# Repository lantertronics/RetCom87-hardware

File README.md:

# RetCom87-hardware
These are expansion boards for the W65C265SXB development board by Western Design Center developed for the "RetCom87" homebrew computer project by my Retrofuturistic Hardware Vertically Integrated Project team at Georgia Tech. For details, see this YouTube playlist:

https://www.youtube.com/playlist?list=PLOunECWxELQQ03GeMmJSVX49A8VtCcbT9

Atari/Sega controller board: This works! See the Wiki for how to read the controller buttons and the example test code.

Sound board: The YM2149 soundchip board design has been tested on the breadboard, but the actual PCB hasn't been tested yet (I need to order it from JLCPCB). See the example test code.

Video board: The reset pin on TMS9118 is erroneously left disconnected on the PCB; I had to add a bodge wire to hook it to the W65C265SXB reset pin. The TMS9118 board currently sends out bright speckled video. I'm not sure what the issue is: https://youtu.be/yKsjV6f-HKg -- if anyone has any advice, please let me know: lanterma@ece.gatech.edu

These designs are dedicated to the public domain.

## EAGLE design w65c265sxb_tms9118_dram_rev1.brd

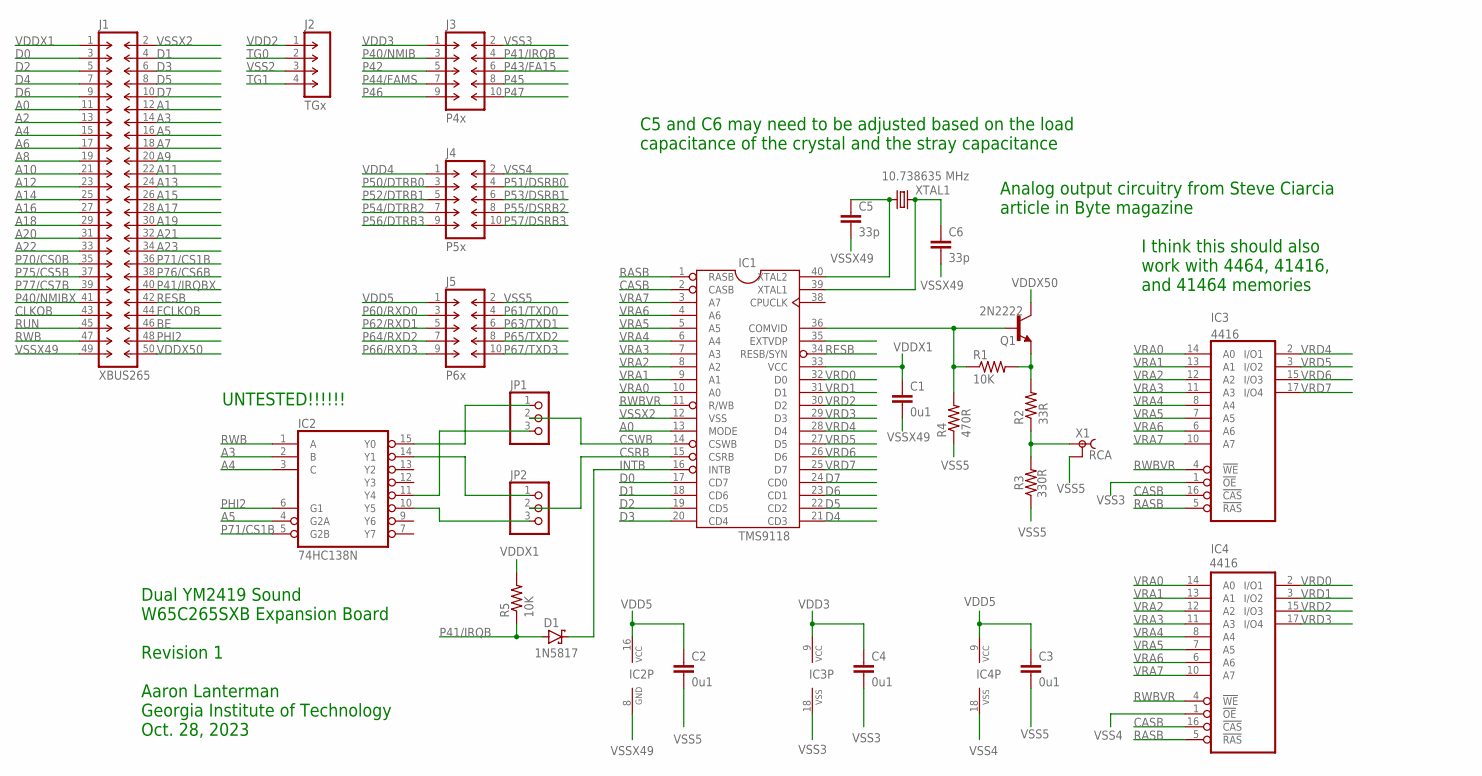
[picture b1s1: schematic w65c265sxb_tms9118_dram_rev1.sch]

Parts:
C1, C2, C3, C4: 0u1; C050-025X075-AARON
C5, C6: 33p; C050-025X075-AARON
D1: 1N5817-B; DO41-7.6
IC1: TMS9118; DIL40
IC2: 74HC138N; DIL16
IC3, IC4: 41464; DIL18
J1: XBUS265; DIL-100-2X25
J2: TGx; SIP-100-04-40
J3: P4x; DIL-100-2X05
J4: P5x; DIL-100-2X05
J5: P6x; DIL-100-2X05
JP1, JP2: PINHD-1X3; 1X03
Q1: 2N2222; TO92-EBC-OVAL
R1, R5: 10K; 0207/10
R2: 33R; 0207/10
R3: 330R; 0207/10
R4: 470R; 0207/10
X1: RCA; TOBU3
XTAL1: 10.738635 MHz; HC49/S

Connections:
A0: IC1.13 (MODE), J1.11
A1: J1.12
A2: J1.13
A3: IC2.2 (B), J1.14
A4: IC2.3 (C), J1.15
A5: IC2.4 (G2A), J1.16
A6: J1.17
A7: J1.18
A8: J1.19
A9: J1.20
A10: J1.21
A11: J1.22
A12: J1.23
A13: J1.24
A14: J1.25
A15: J1.26
A16: J1.27
A17: J1.28
A18: J1.29
A19: J1.30
A20: J1.31
A21: J1.32
A22: J1.33
A23: J1.34
BE: J1.46
CASB: IC1.2 (CASB), IC3.16 (!CAS), IC4.16 (!CAS)
CLKOB: J1.43
CSRB: IC1.15 (CSRB), JP2.2
CSWB: IC1.14 (CSWB), JP1.2
D0: IC1.17 (CD7), J1.3
D1: IC1.18 (CD6), J1.4
D2: IC1.19 (CD5), J1.5
D3: IC1.20 (CD4), J1.6
D4: IC1.21 (CD3), J1.7
D5: IC1.22 (CD2), J1.8
D6: IC1.23 (CD1), J1.9
D7: IC1.24 (CD0), J1.10
FCLKOB: J1.44
INTB: D1.C, IC1.16 (INTB)
unnamed: IC2.15 (Y0), JP1.1
unnamed: IC2.14 (Y1), JP2.1
unnamed: Q1.E, R1.2, R2.2
unnamed: R2.1, R3.2, X1.1
unnamed: IC2.11 (Y4), JP1.3
unnamed: IC2.10 (Y5), JP2.3
unnamed: IC1.36 (COMVID), Q1.B, R1.1, R4.2
P40/NMIB: J3.3
P40/NMIBX: J1.41
P41/IRQB: D1.A, J3.4, R5.1
P41/IRQBX: J1.40
P42: J3.5
P43/FA15: J3.6
P44/FAMS: J3.7
P45: J3.8
P46: J3.9
P47: J3.10
P50/DTRB0: J4.3
P51/DSRB0: J4.4
P52/DTRB1: J4.5
P53/DSRB1: J4.6
P54/DTRB2: J4.7
P55/DSRB2: J4.8
P56/DTRB3: J4.9
P57/DSRB3: J4.10
P60/RXD0: J5.3
P61/TXD0: J5.4
P62/RXD1: J5.5
P63/TXD1: J5.6
P64/RXD2: J5.7
P65/TXD2: J5.8
P66/RXD3: J5.9
P67/TXD3: J5.10
P70/CS0B: J1.35
P71/CS1B: IC2.5 (G2B), J1.36
P75/CS5B: J1.37
P76/CS6B: J1.38
P77/CS7B: J1.39
PHI2: IC2.6 (G1), J1.48
RASB: IC1.1 (RASB), IC3.5 (!RAS), IC4.5 (!RAS)
RESB: IC1.34 (RESB/SYN), J1.42
RUN: J1.45
RWB: IC2.1 (A), J1.47
RWBVR: IC1.11 (R/WB), IC3.4 (!WE), IC4.4 (!WE)
TG0: J2.2
TG1: J2.4
VDD2: J2.1
VDD3: C4.1, IC3.9 (VCC), J3.1
VDD4: J4.1
VDD5: C2.1, C3.1, IC2.16 (VCC), IC4.9 (VCC), J5.1
VDDX1: C1.1, IC1.33 (VCC), J1.1, R5.2
VDDX50: J1.50, Q1.C
VRA0: IC1.10 (A0), IC3.14 (A0), IC4.14 (A0)
VRA1: IC1.9 (A1), IC3.13 (A1), IC4.13 (A1)
VRA2: IC1.8 (A2), IC3.12 (A2), IC4.12 (A2)
VRA3: IC1.7 (A3), IC3.11 (A3), IC4.11 (A3)
VRA4: IC1.6 (A4), IC3.8 (A4), IC4.8 (A4)
VRA5: IC1.5 (A5), IC3.7 (A5), IC4.7 (A5)
VRA6: IC1.4 (A6), IC3.6 (A6), IC4.6 (A6)
VRA7: IC1.3 (A7), IC3.10 (A7), IC4.10 (A7)
VRD0: IC1.32 (D0), IC4.2 (I/O1)
VRD1: IC1.31 (D1), IC4.3 (I/O2)
VRD2: IC1.30 (D2), IC4.15 (I/O3)
VRD3: IC1.29 (D3), IC4.17 (I/O4)
VRD4: IC1.28 (D4), IC3.2 (I/O1)
VRD5: IC1.27 (D5), IC3.3 (I/O2)
VRD6: IC1.26 (D6), IC3.15 (I/O3)
VRD7: IC1.25 (D7), IC3.17 (I/O4)
VSS2: J2.3
VSS3: C4.2, IC3.1 (!OE), IC3.18 (VSS), J3.2
VSS4: IC4.1 (!OE), IC4.18 (VSS), J4.2
VSS5: C2.2, C3.2, J5.2, R3.1, R4.1, X1.2, X1.2@1 (2), X1.2@2 (2)
VSSX2: IC1.12 (VSS), J1.2
VSSX49: C1.2, C5.2, C6.2, IC2.8 (GND), J1.49
XTAL1: C6.1, IC1.39 (XTAL1), XTAL1.2
XTAL2: C5.1, IC1.40 (XTAL2), XTAL1.1

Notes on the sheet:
Dual YM2419 Sound W65C265SXB Expansion Board Revision 1 Aaron Lanterman Georgia Institute of Technology Oct. 28, 2023
UNTESTED!!!!!!
4416
I think this should also work with 4464, 41416, and 41464 memories
C5 and C6 may need to be adjusted based on the load capacitance of the crystal and the stray capacitance
Analog output circuitry from Steve Ciarcia article in Byte magazine
1N5817

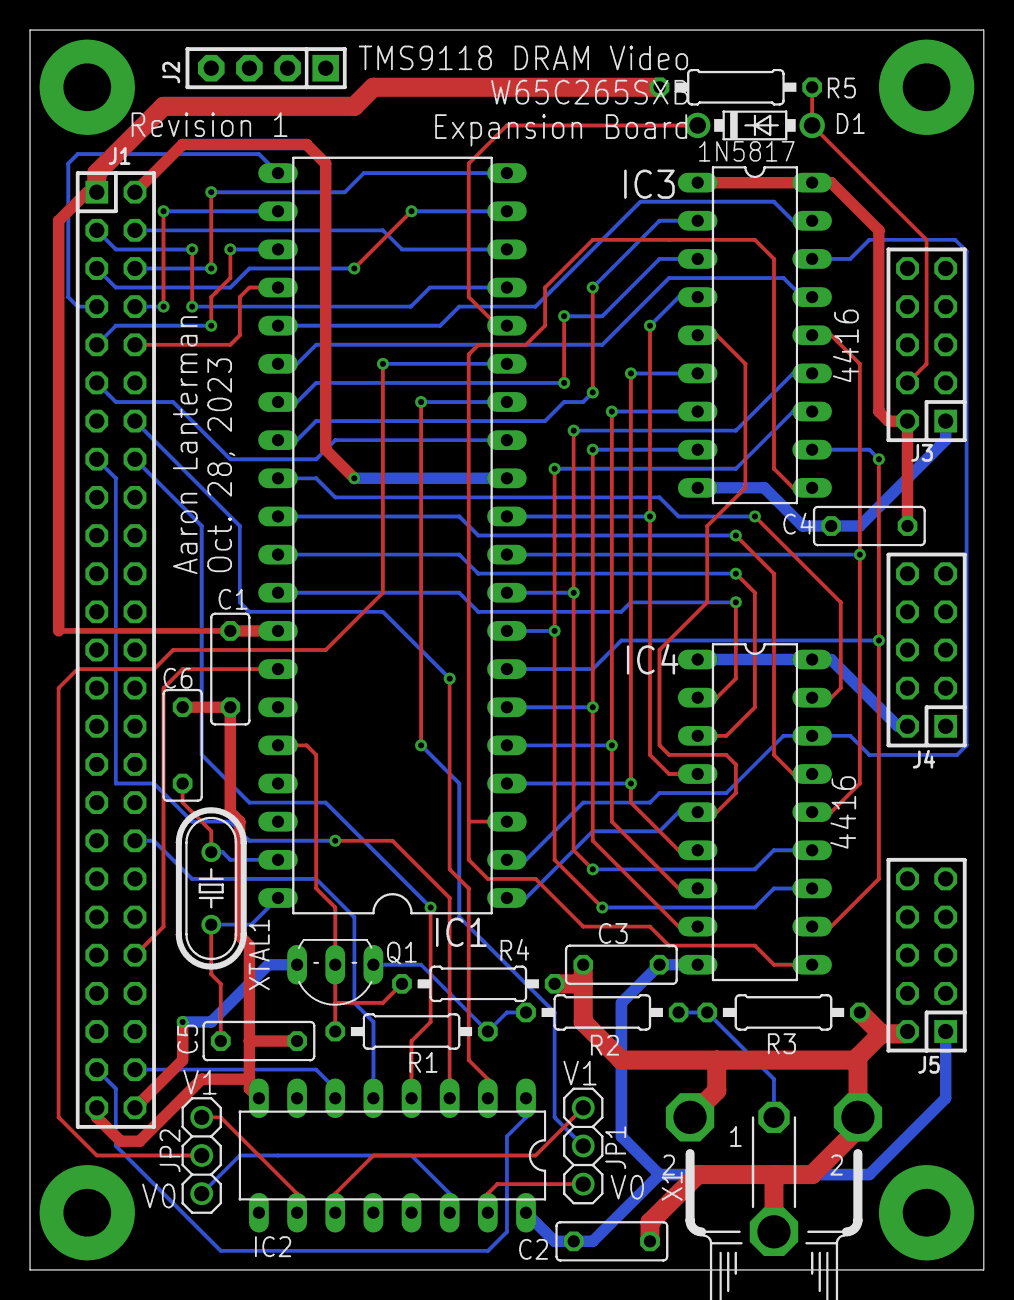
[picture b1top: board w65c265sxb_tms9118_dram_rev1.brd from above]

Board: 2 copper layers, 63.5 x 82.5 mm, 26 parts (0 on the bottom side), 57 nets.

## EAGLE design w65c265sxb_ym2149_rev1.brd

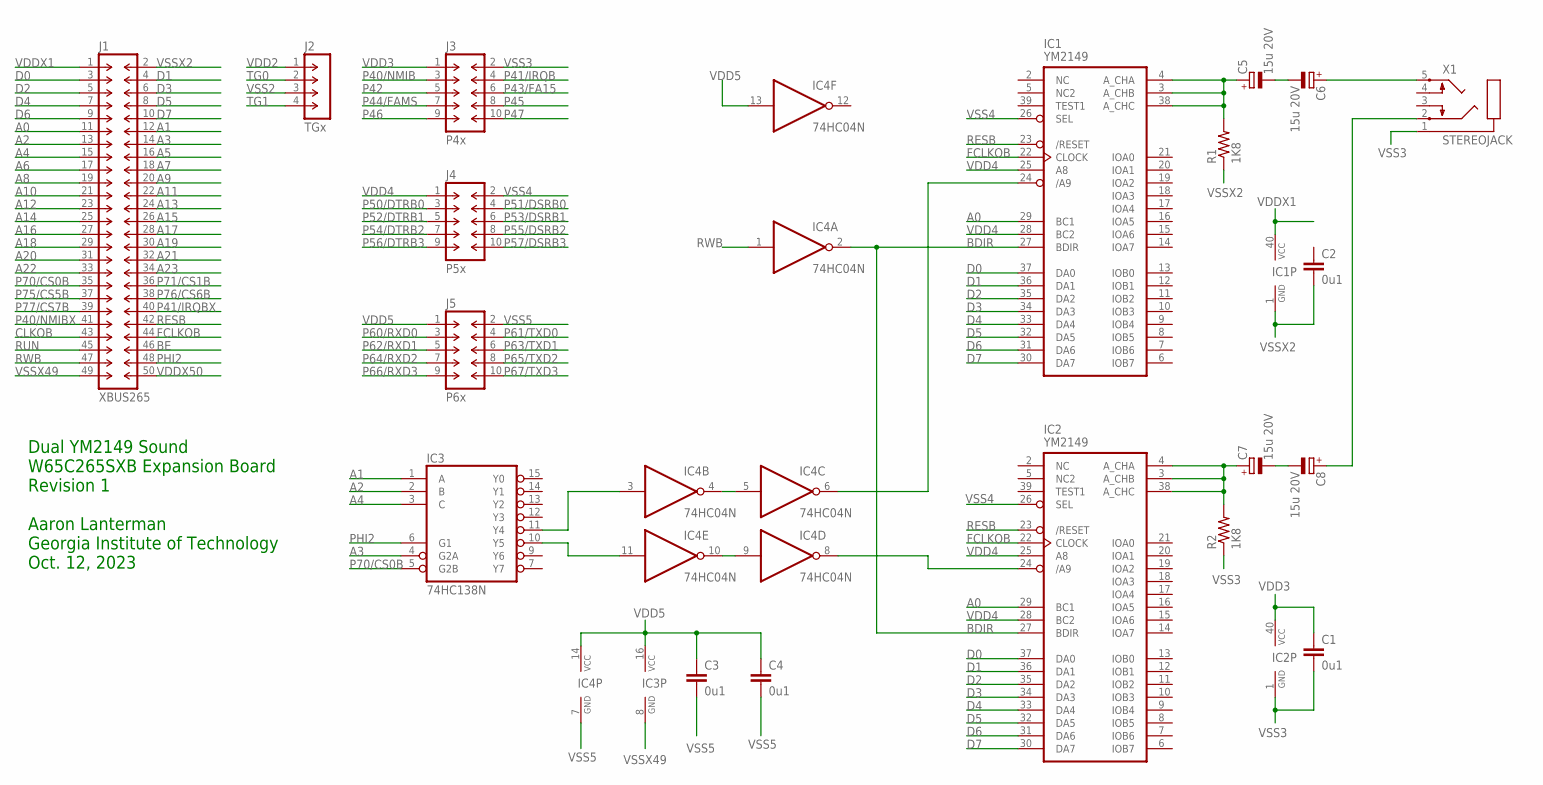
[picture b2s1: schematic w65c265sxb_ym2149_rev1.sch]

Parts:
C1, C2, C3, C4: 0u1; C050-025X075-AARON
C5, C6, C7, C8: 15u 20V; E2,5-7
IC1, IC2: YM2149; DIL40
IC3: 74HC138N; DIL16
IC4: 74HC04N; DIL14
J1: XBUS265; DIL-100-2X25
J2: TGx; SIP-100-04-40
J3: P4x; DIL-100-2X05
J4: P5x; DIL-100-2X05
J5: P6x; DIL-100-2X05
R1, R2: 1K8; 0207/10
X1: STEREOJACK; STX3100

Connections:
A0: IC1.29 (BC1), IC2.29 (BC1), J1.11
A1: IC3.1 (A), J1.12
A2: IC3.2 (B), J1.13
A3: IC3.4 (G2A), J1.14
A4: IC3.3 (C), J1.15
A5: J1.16
A6: J1.17
A7: J1.18
A8: J1.19
A9: J1.20
A10: J1.21
A11: J1.22
A12: J1.23
A13: J1.24
A14: J1.25
A15: J1.26
A16: J1.27
A17: J1.28
A18: J1.29
A19: J1.30
A20: J1.31
A21: J1.32
A22: J1.33
A23: J1.34
BDIR: IC1.27 (BDIR), IC2.27 (BDIR), IC4.2 (O)
BE: J1.46
CLKOB: J1.43
D0: IC1.37 (DA0), IC2.37 (DA0), J1.3
D1: IC1.36 (DA1), IC2.36 (DA1), J1.4
D2: IC1.35 (DA2), IC2.35 (DA2), J1.5
D3: IC1.34 (DA3), IC2.34 (DA3), J1.6
D4: IC1.33 (DA4), IC2.33 (DA4), J1.7
D5: IC1.32 (DA5), IC2.32 (DA5), J1.8
D6: IC1.31 (DA6), IC2.31 (DA6), J1.9
D7: IC1.30 (DA7), IC2.30 (DA7), J1.10
FCLKOB: IC1.22 (CLOCK), IC2.22 (CLOCK), J1.44
unnamed: IC3.11 (Y4), IC4.3 (I)
unnamed: IC4.4 (O), IC4.5 (I)
unnamed: IC4.9 (I), IC4.10 (O)
unnamed: IC1.24 (/A9), IC4.6 (O)
unnamed: IC3.10 (Y5), IC4.11 (I)
unnamed: C5.+, IC1.3 (A_CHB), IC1.4 (A_CHA), IC1.38 (A_CHC), R1.2
unnamed: C7.+, IC2.3 (A_CHB), IC2.4 (A_CHA), IC2.38 (A_CHC), R2.2
unnamed: IC2.24 (/A9), IC4.8 (O)
unnamed: C5.-, C6.-
unnamed: C7.-, C8.-
unnamed: C6.+, X1.5
unnamed: C8.+, X1.2
P40/NMIB: J3.3
P40/NMIBX: J1.41
P41/IRQB: J3.4
P41/IRQBX: J1.40
P42: J3.5
P43/FA15: J3.6
P44/FAMS: J3.7
P45: J3.8
P46: J3.9
P47: J3.10
P50/DTRB0: J4.3
P51/DSRB0: J4.4
P52/DTRB1: J4.5
P53/DSRB1: J4.6
P54/DTRB2: J4.7
P55/DSRB2: J4.8
P56/DTRB3: J4.9
P57/DSRB3: J4.10
P60/RXD0: J5.3
P61/TXD0: J5.4
P62/RXD1: J5.5
P63/TXD1: J5.6
P64/RXD2: J5.7
P65/TXD2: J5.8
P66/RXD3: J5.9
P67/TXD3: J5.10
P70/CS0B: IC3.5 (G2B), J1.35
P71/CS1B: J1.36
P75/CS5B: J1.37
P76/CS6B: J1.38
P77/CS7B: J1.39
PHI2: IC3.6 (G1), J1.48
RESB: IC1.23 (/RESET), IC2.23 (/RESET), J1.42
RUN: J1.45
RWB: IC4.1 (I), J1.47
TG0: J2.2
TG1: J2.4
VDD2: J2.1
VDD3: C1.1, IC2.40 (VCC), J3.1
VDD4: IC1.25 (A8), IC1.28 (BC2), IC2.25 (A8), IC2.28 (BC2), J4.1
VDD5: C3.1, C4.1, IC3.16 (VCC), IC4.13 (I), IC4.14 (VCC), J5.1
VDDX1: IC1.40 (VCC), J1.1
VDDX50: J1.50
VSS2: J2.3
VSS3: C1.2, IC2.1 (GND), J3.2, R2.1, X1.1
VSS4: IC1.26 (SEL), IC2.26 (SEL), J4.2
VSS5: C3.2, C4.2, IC4.7 (GND), J5.2
VSSX2: C2.2, IC1.1 (GND), J1.2, R1.1
VSSX49: IC3.8 (GND), J1.49

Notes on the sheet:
Dual YM2149 Sound W65C265SXB Expansion Board Revision 1 Aaron Lanterman Georgia Institute of Technology Oct. 12, 2023

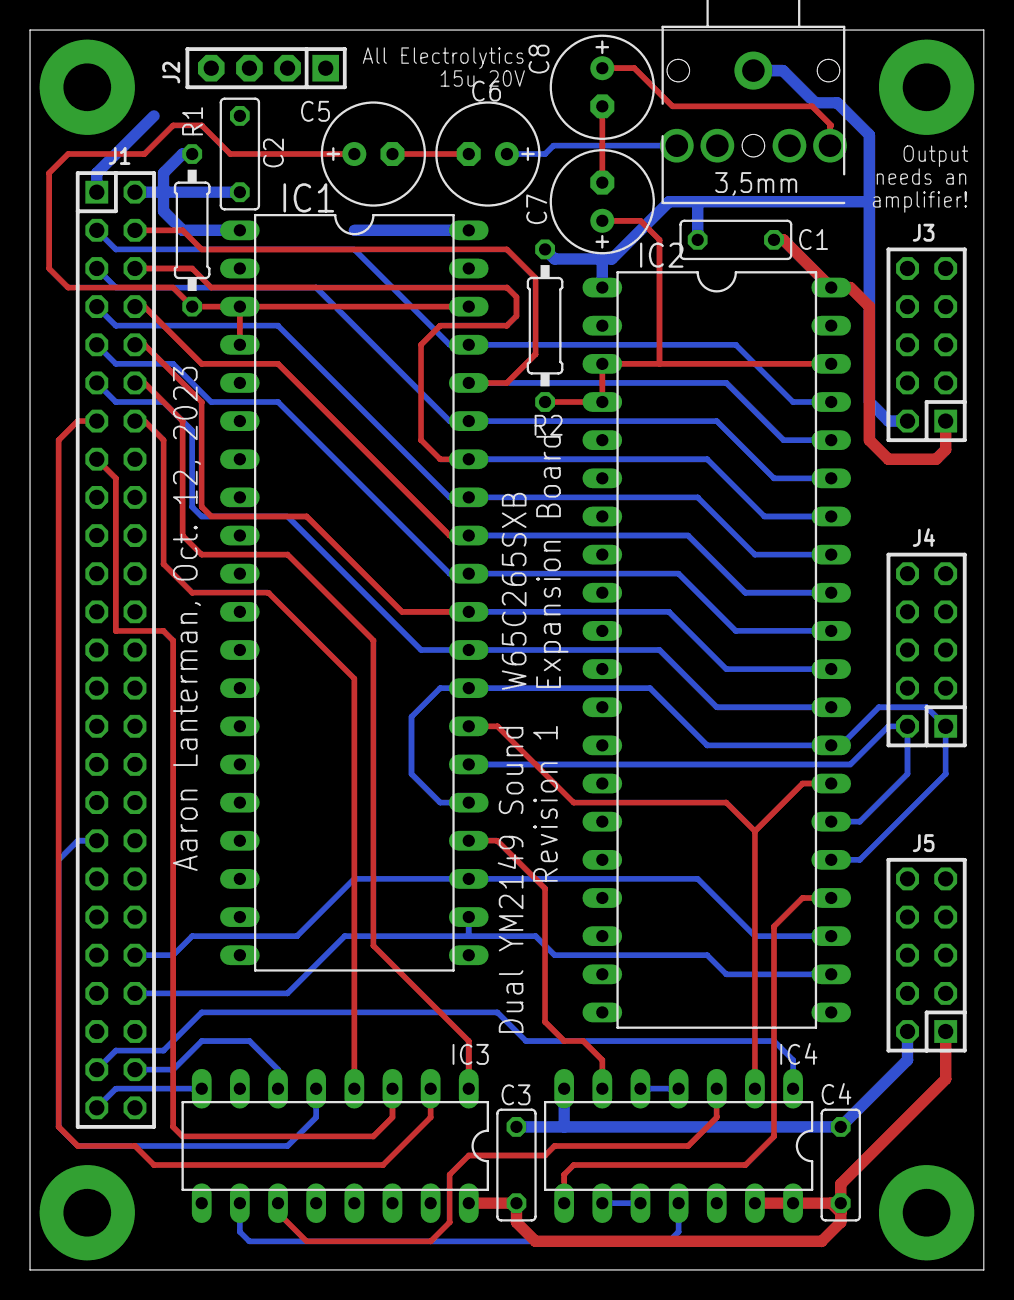
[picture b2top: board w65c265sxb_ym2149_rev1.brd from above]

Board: 2 copper layers, 63.5 x 82.5 mm, 20 parts (0 on the bottom side), 40 nets.

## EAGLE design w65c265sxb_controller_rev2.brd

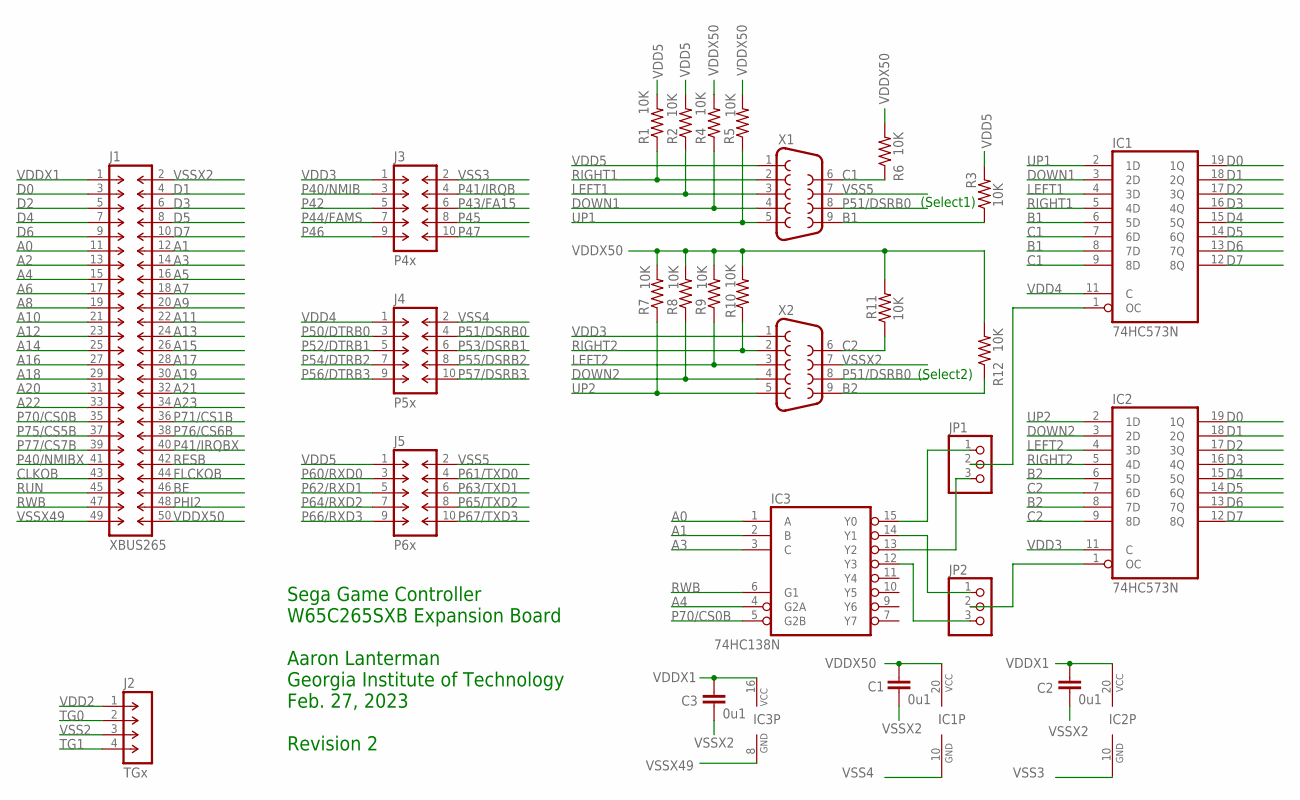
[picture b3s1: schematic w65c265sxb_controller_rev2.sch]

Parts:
C1, C2, C3: 0u1; C050-025X075-AARON
IC1, IC2: 74HC573N; DIL20
IC3: 74HC138N; DIL16
J1: XBUS265; DIL-100-2X25
J2: TGx; SIP-100-04-40
J3: P4x; DIL-100-2X05
J4: P5x; DIL-100-2X05
J5: P6x; DIL-100-2X05
JP1, JP2: PINHD-1X3; 1X03
R1, R2, R3, R4, R5, R6, R7, R8, R9, R10, R11, R12: 10K; 0207/10
X1, X2: F09HP

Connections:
A0: IC3.1 (A), J1.11
A1: IC3.2 (B), J1.12
A2: J1.13
A3: IC3.3 (C), J1.14
A4: IC3.4 (G2A), J1.15
A5: J1.16
A6: J1.17
A7: J1.18
A8: J1.19
A9: J1.20
A10: J1.21
A11: J1.22
A12: J1.23
A13: J1.24
A14: J1.25
A15: J1.26
A16: J1.27
A17: J1.28
A18: J1.29
A19: J1.30
A20: J1.31
A21: J1.32
A22: J1.33
A23: J1.34
B1: IC1.6 (5D), IC1.8 (7D), R3.1, X1.9
B2: IC2.6 (5D), IC2.8 (7D), R12.1, X2.9
BE: J1.46
C1: IC1.7 (6D), IC1.9 (8D), R6.1, X1.6
C2: IC2.7 (6D), IC2.9 (8D), R11.1, X2.6
CLKOB: J1.43
D0: IC1.19 (1Q), IC2.19 (1Q), J1.3
D1: IC1.18 (2Q), IC2.18 (2Q), J1.4
D2: IC1.17 (3Q), IC2.17 (3Q), J1.5
D3: IC1.16 (4Q), IC2.16 (4Q), J1.6
D4: IC1.15 (5Q), IC2.15 (5Q), J1.7
D5: IC1.14 (6Q), IC2.14 (6Q), J1.8
D6: IC1.13 (7Q), IC2.13 (7Q), J1.9
D7: IC1.12 (8Q), IC2.12 (8Q), J1.10
DOWN1: IC1.3 (2D), R4.1, X1.4
DOWN2: IC2.3 (2D), R8.1, X2.4
FLCKOB: J1.44
LEFT1: IC1.4 (3D), R2.1, X1.3
LEFT2: IC2.4 (3D), R9.1, X2.3
unnamed: IC3.15 (Y0), JP1.1
unnamed: IC3.13 (Y2), JP1.3
unnamed: IC1.1 (OC), JP1.2
unnamed: IC3.14 (Y1), JP2.1
unnamed: IC3.12 (Y3), JP2.3
unnamed: IC2.1 (OC), JP2.2
P40/NMIB: J3.3
P40/NMIBX: J1.41
P41/IRQB: J3.4
P41/IRQBX: J1.40
P42: J3.5
P43/FA15: J3.6
P44/FAMS: J3.7
P45: J3.8
P46: J3.9
P47: J3.10
P50/DTRB0: J4.3
P51/DSRB0: J4.4, X1.8, X2.8
P52/DTRB1: J4.5
P53/DSRB1: J4.6
P54/DTRB2: J4.7
P55/DSRB2: J4.8
P56/DTRB3: J4.9
P57/DSRB3: J4.10
P60/RXD0: J5.3
P61/TXD0: J5.4
P62/RXD1: J5.5
P63/TXD1: J5.6
P64/RXD2: J5.7
P65/TXD2: J5.8
P66/RXD3: J5.9
P67/TXD3: J5.10
P70/CS0B: IC3.5 (G2B), J1.35
P71/CS1B: J1.36
P75/CS5B: J1.37
P76/CS6B: J1.38
P77/CS7B: J1.39
PHI2: J1.48
RESB: J1.42
RIGHT1: IC1.5 (4D), R1.1, X1.2
RIGHT2: IC2.5 (4D), R10.1, X2.2
RUN: J1.45
RWB: IC3.6 (G1), J1.47
TG0: J2.2
TG1: J2.4
UP1: IC1.2 (1D), R5.1, X1.5
UP2: IC2.2 (1D), R7.1, X2.5
VDD2: J2.1
VDD3: IC2.11 (C), J3.1, X2.1
VDD4: IC1.11 (C), J4.1
VDD5: J5.1, R1.2, R2.2, R3.2, X1.1
VDDX1: C2.1, C3.1, IC2.20 (VCC), IC3.16 (VCC), J1.1
VDDX50: C1.1, IC1.20 (VCC), J1.50, R4.2, R5.2, R6.2, R7.2, R8.2, R9.2, R10.2, R11.2, R12.2
VSS2: J2.3
VSS3: IC2.10 (GND), J3.2
VSS4: IC1.10 (GND), J4.2
VSS5: J5.2, X1.7
VSSX2: C1.2, C2.2, C3.2, J1.2, X2.7
VSSX49: IC3.8 (GND), J1.49

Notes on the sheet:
Sega Game Controller W65C265SXB Expansion Board Aaron Lanterman Georgia Institute of Technology Feb. 27, 2023 Revision 2
(Select1)
(Select2)

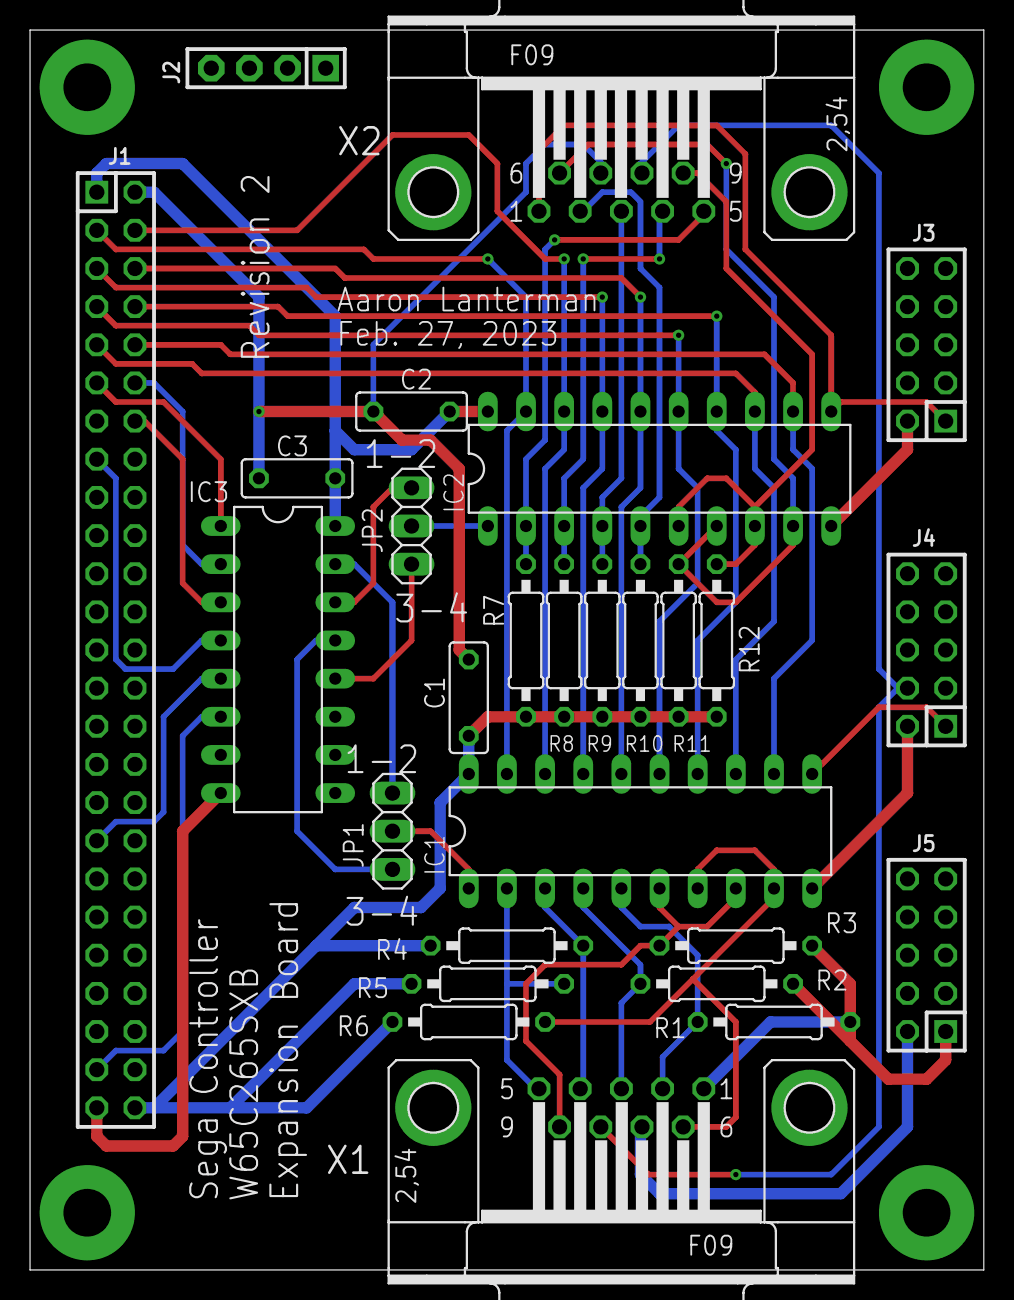
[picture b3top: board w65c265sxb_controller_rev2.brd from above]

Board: 2 copper layers, 63.5 x 82.5 mm, 27 parts (0 on the bottom side), 43 nets.

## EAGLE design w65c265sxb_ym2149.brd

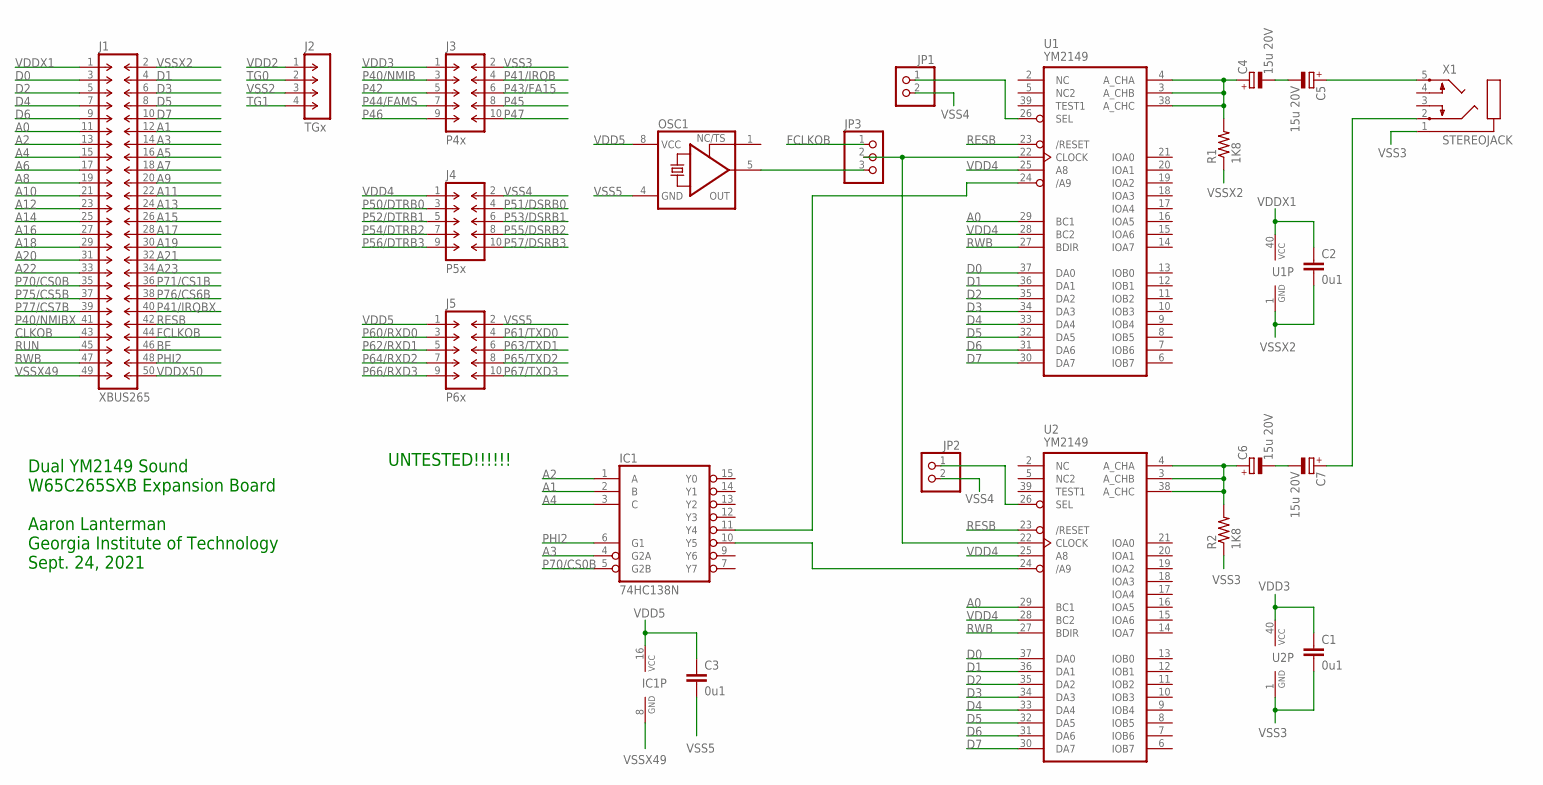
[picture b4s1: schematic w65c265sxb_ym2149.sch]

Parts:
C1, C2, C3: 0u1; C050-025X075-AARON
C4, C5, C6, C7: 15u 20V; E2,5-7
IC1: 74HC138N; DIL16
J1: XBUS265; DIL-100-2X25
J2: TGx; SIP-100-04-40
J3: P4x; DIL-100-2X05
J4: P5x; DIL-100-2X05
J5: P6x; DIL-100-2X05
JP1, JP2: PINHD-1X2; 1X02
JP3: PINHD-1X3; 1X03
OSC1: XO-8; DIL08S
R1, R2: 1K8; 0207/10
U1, U2: YM2149; DIL40
X1: STEREOJACK; STX3100

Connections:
A0: J1.11, U1.29 (BC1), U2.29 (BC1)
A1: IC1.2 (B), J1.12
A2: IC1.1 (A), J1.13
A3: IC1.4 (G2A), J1.14
A4: IC1.3 (C), J1.15
A5: J1.16
A6: J1.17
A7: J1.18
A8: J1.19
A9: J1.20
A10: J1.21
A11: J1.22
A12: J1.23
A13: J1.24
A14: J1.25
A15: J1.26
A16: J1.27
A17: J1.28
A18: J1.29
A19: J1.30
A20: J1.31
A21: J1.32
A22: J1.33
A23: J1.34
BE: J1.46
CLKOB: J1.43
D0: J1.3, U1.37 (DA0), U2.37 (DA0)
D1: J1.4, U1.36 (DA1), U2.36 (DA1)
D2: J1.5, U1.35 (DA2), U2.35 (DA2)
D3: J1.6, U1.34 (DA3), U2.34 (DA3)
D4: J1.7, U1.33 (DA4), U2.33 (DA4)
D5: J1.8, U1.32 (DA5), U2.32 (DA5)
D6: J1.9, U1.31 (DA6), U2.31 (DA6)
D7: J1.10, U1.30 (DA7), U2.30 (DA7)
FCLKOB: J1.44, JP3.1
unnamed: JP1.1, U1.26 (SEL)
unnamed: JP3.2, U1.22 (CLOCK), U2.22 (CLOCK)
unnamed: JP3.3, OSC1.5 (OUT)
unnamed: IC1.11 (Y4), U1.24 (/A9)
unnamed: IC1.10 (Y5), U2.24 (/A9)
unnamed: C4.+, R1.2, U1.3 (A_CHB), U1.4 (A_CHA), U1.38 (A_CHC)
unnamed: C6.+, R2.2, U2.3 (A_CHB), U2.4 (A_CHA), U2.38 (A_CHC)
unnamed: JP2.1, U2.26 (SEL)
unnamed: C4.-, C5.-
unnamed: C6.-, C7.-
unnamed: C5.+, X1.5
unnamed: C7.+, X1.2
P40/NMIB: J3.3
P40/NMIBX: J1.41
P41/IRQB: J3.4
P41/IRQBX: J1.40
P42: J3.5
P43/FA15: J3.6
P44/FAMS: J3.7
P45: J3.8
P46: J3.9
P47: J3.10
P50/DTRB0: J4.3
P51/DSRB0: J4.4
P52/DTRB1: J4.5
P53/DSRB1: J4.6
P54/DTRB2: J4.7
P55/DSRB2: J4.8
P56/DTRB3: J4.9
P57/DSRB3: J4.10
P60/RXD0: J5.3
P61/TXD0: J5.4
P62/RXD1: J5.5
P63/TXD1: J5.6
P64/RXD2: J5.7
P65/TXD2: J5.8
P66/RXD3: J5.9
P67/TXD3: J5.10
P70/CS0B: IC1.5 (G2B), J1.35
P71/CS1B: J1.36
P75/CS5B: J1.37
P76/CS6B: J1.38
P77/CS7B: J1.39
PHI2: IC1.6 (G1), J1.48
RESB: J1.42, U1.23 (/RESET), U2.23 (/RESET)
RUN: J1.45
RWB: J1.47, U1.27 (BDIR), U2.27 (BDIR)
TG0: J2.2
TG1: J2.4
VDD2: J2.1
VDD3: C1.1, J3.1, U2.40 (VCC)
VDD4: J4.1, U1.25 (A8), U1.28 (BC2), U2.25 (A8), U2.28 (BC2)
VDD5: C3.1, IC1.16 (VCC), J5.1, OSC1.8 (VCC)
VDDX1: C2.1, J1.1, U1.40 (VCC)
VDDX50: J1.50
VSS2: J2.3
VSS3: C1.2, J3.2, R2.1, U2.1 (GND), X1.1
VSS4: J4.2, JP1.2, JP2.2
VSS5: C3.2, J5.2, OSC1.4 (GND)
VSSX2: C2.2, J1.2, R1.1, U1.1 (GND)
VSSX49: IC1.8 (GND), J1.49

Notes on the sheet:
Dual YM2149 Sound W65C265SXB Expansion Board Aaron Lanterman Georgia Institute of Technology Sept. 24, 2021
UNTESTED!!!!!!

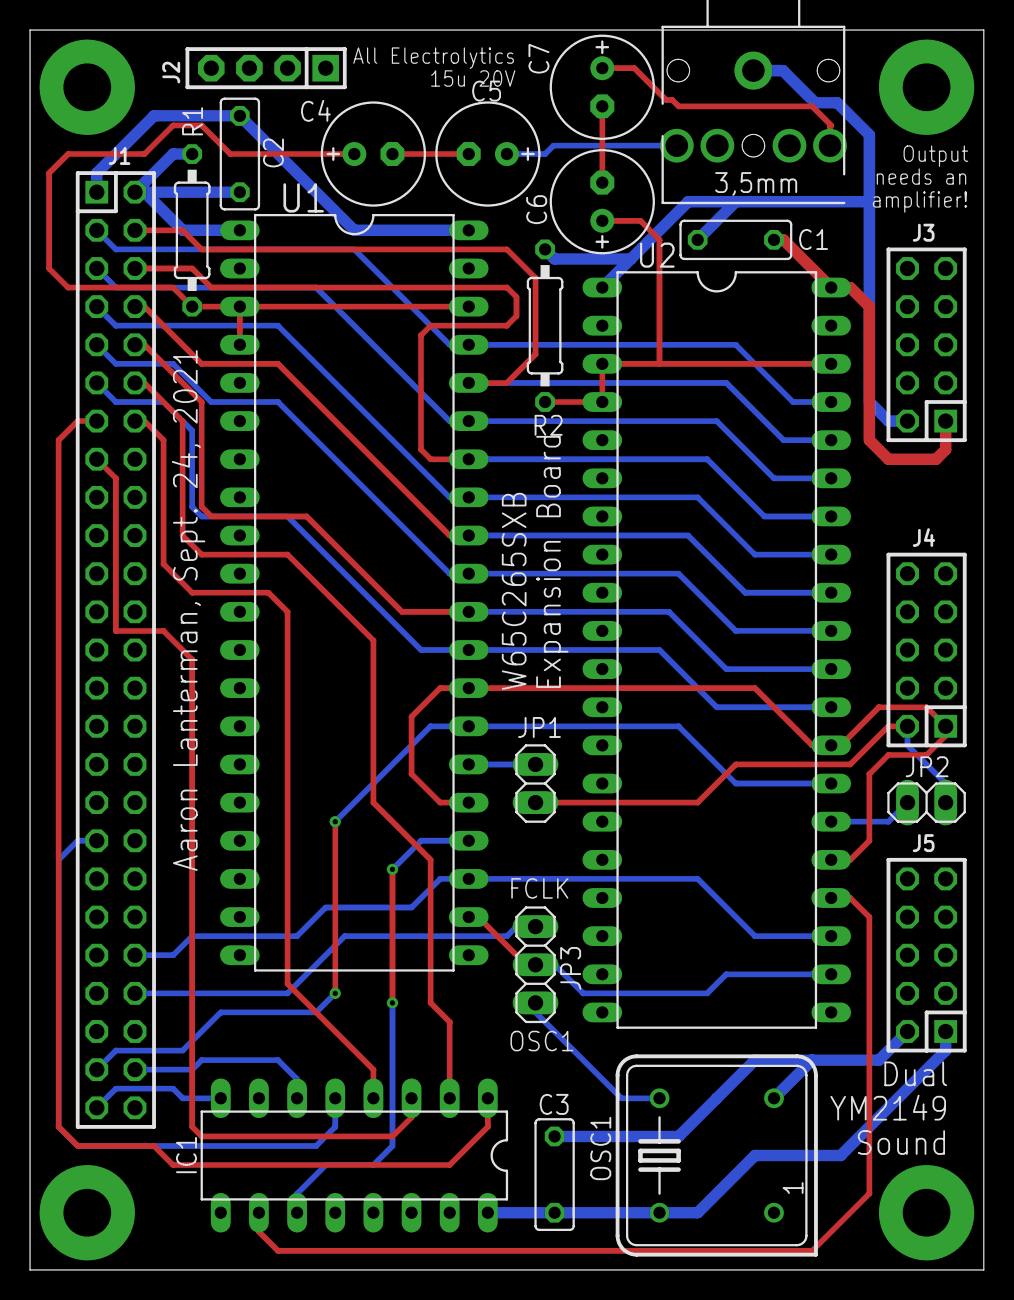
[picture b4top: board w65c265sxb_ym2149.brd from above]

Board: 2 copper layers, 63.5 x 82.5 mm, 22 parts (0 on the bottom side), 39 nets.

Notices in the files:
parts and their libraries:
con-headers-jp: Copyright (C) 2008, Bob Starr
